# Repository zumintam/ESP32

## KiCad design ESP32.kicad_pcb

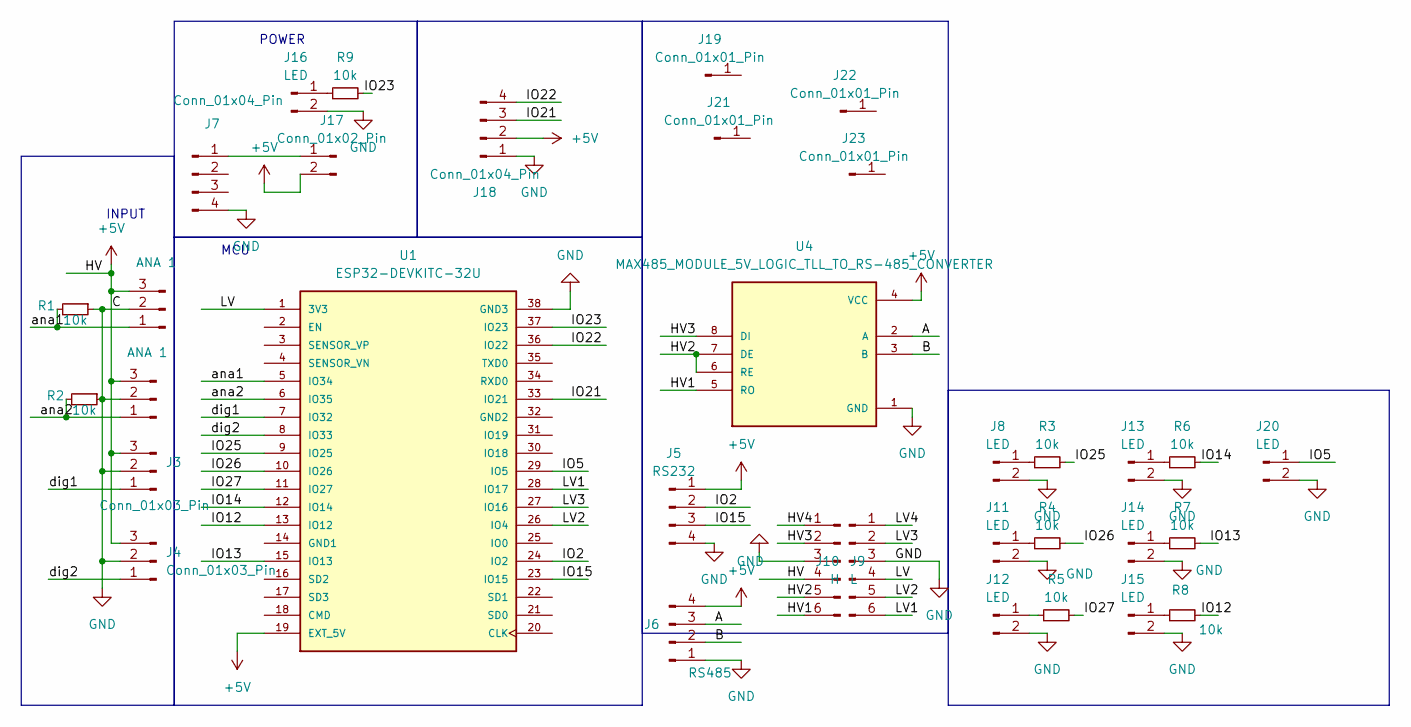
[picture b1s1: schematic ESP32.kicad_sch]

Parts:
J1, J2: ANA 1; JST_EH_S3B-EH_1x03_P2.50mm_Horizontal
J3, J4: Conn_01x03_Pin; JST_EH_S3B-EH_1x03_P2.50mm_Horizontal
J5: RS232; JST_EH_S4B-EH_1x04_P2.50mm_Horizontal
J6: RS485; JST_EH_S4B-EH_1x04_P2.50mm_Horizontal
J7: Conn_01x04_Pin; PinHeader_1x04_P2.54mm_Vertical
J8, J11, J12, J13, J14, J15, J16, J20: LED; JST_XH_B2B-XH-A_1x02_P2.50mm_Vertical
J9: L; PinHeader_1x06_P2.54mm_Vertical
J10: H; PinHeader_1x06_P2.54mm_Vertical
J17: Conn_01x02_Pin; JST_XH_B2B-XH-A_1x02_P2.50mm_Vertical
J18: Conn_01x04_Pin; JST_XH_B4B-XH-A_1x04_P2.50mm_Vertical
J19, J21, J22, J23: Conn_01x01_Pin; MountingHole_2.2mm_M2_Pad
R1, R2, R3, R4, R5, R6, R7, R8, R9: 10k; R_0805_2012Metric
U1: ESP32-DEVKITC-32U; MODULE_ESP32-DEVKITC-32U; PARTREV V4
U4: MAX485_MODULE_5V_LOGIC_TLL_TO_RS-485_CONVERTER; MODULE_MAX485_MODULE_5V_LOGIC_TLL_TO_RS-485_CONVERTER; PARTREV 1r0

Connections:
/A: J6.3, U4.2 (A)
/B: J6.2, U4.3 (B)
/HV1: J9.6, U4.5 (RO)
/HV2: J9.5, U4.6 (RE), U4.7 (DE)
/HV3: J9.2, U4.8 (DI)
/HV4: J9.1
/IO2: J5.2, U1.24 (IO2)
/IO5: J20.1, U1.29 (IO5)
/IO12: R8.2, U1.13 (IO12)
/IO13: R7.2, U1.15 (IO13)
/IO14: R6.2, U1.12 (IO14)
/IO15: J5.3, U1.23 (IO15)
/IO21: J18.3, U1.33 (IO21)
/IO22: J18.4, U1.36 (IO22)
/IO23: R9.2, U1.37 (IO23)
/IO25: R3.2, U1.9 (IO25)
/IO26: R4.2, U1.10 (IO26)
/IO27: R5.2, U1.11 (IO27)
/LV: J10.4, U1.1 (3V3)
/LV1: J10.6, U1.28 (IO17)
/LV2: J10.5, U1.26 (IO4)
/LV3: J10.2, U1.27 (IO16)
/LV4: J10.1
/ana1: J1.1, R1.2, U1.5 (IO34)
/ana2: J2.1, R2.2, U1.6 (IO35)
/dig1: J3.1, U1.7 (IO32)
/dig2: J4.1, U1.8 (IO33)
unnamed: J8.1, R3.1
unnamed: J11.1, R4.1
unnamed: J12.1, R5.1
unnamed: J13.1, R6.1
unnamed: J14.1, R7.1
unnamed: J15.1, R8.1
unnamed: J16.1, R9.1
unnamed: J7.1, J17.1

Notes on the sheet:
POWER
MCU
INPUT

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
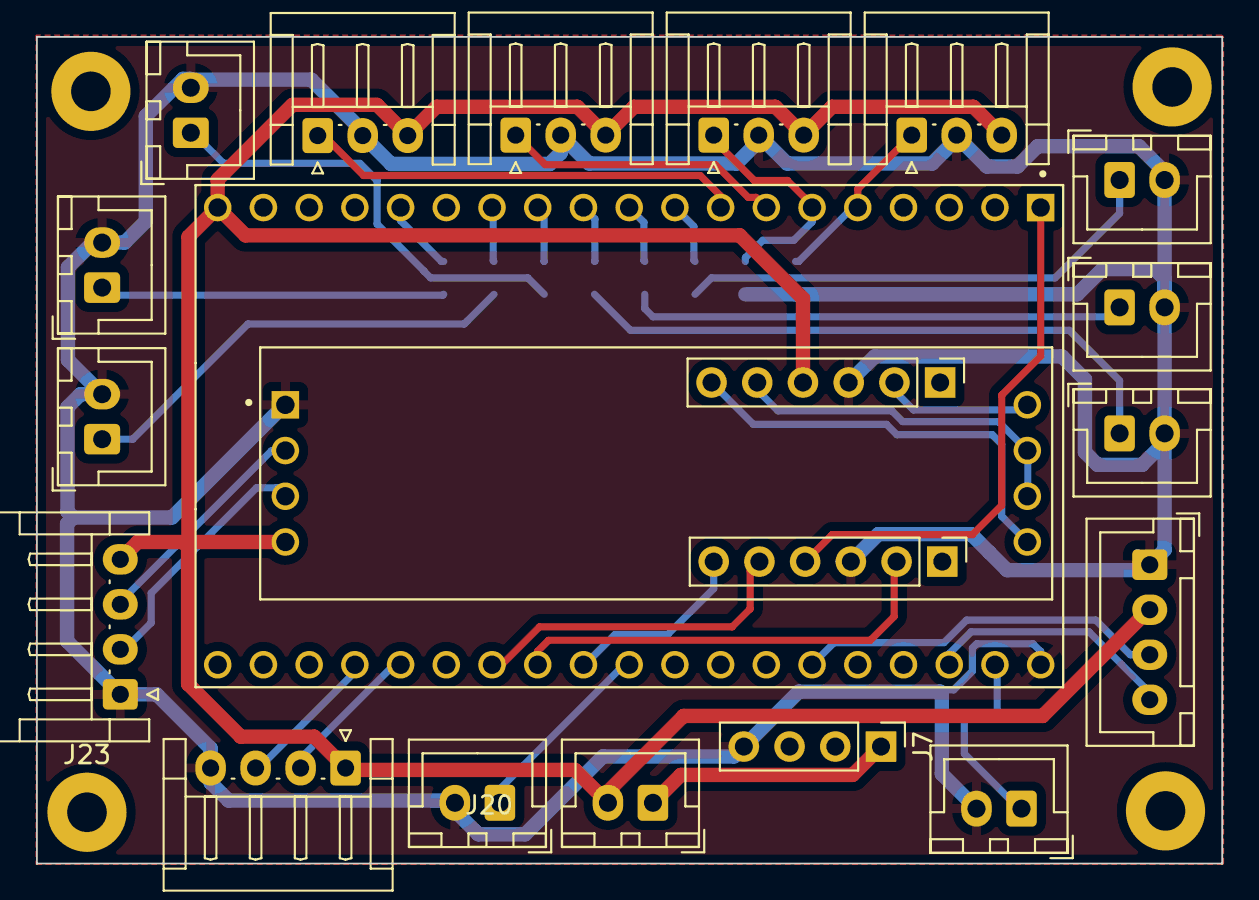
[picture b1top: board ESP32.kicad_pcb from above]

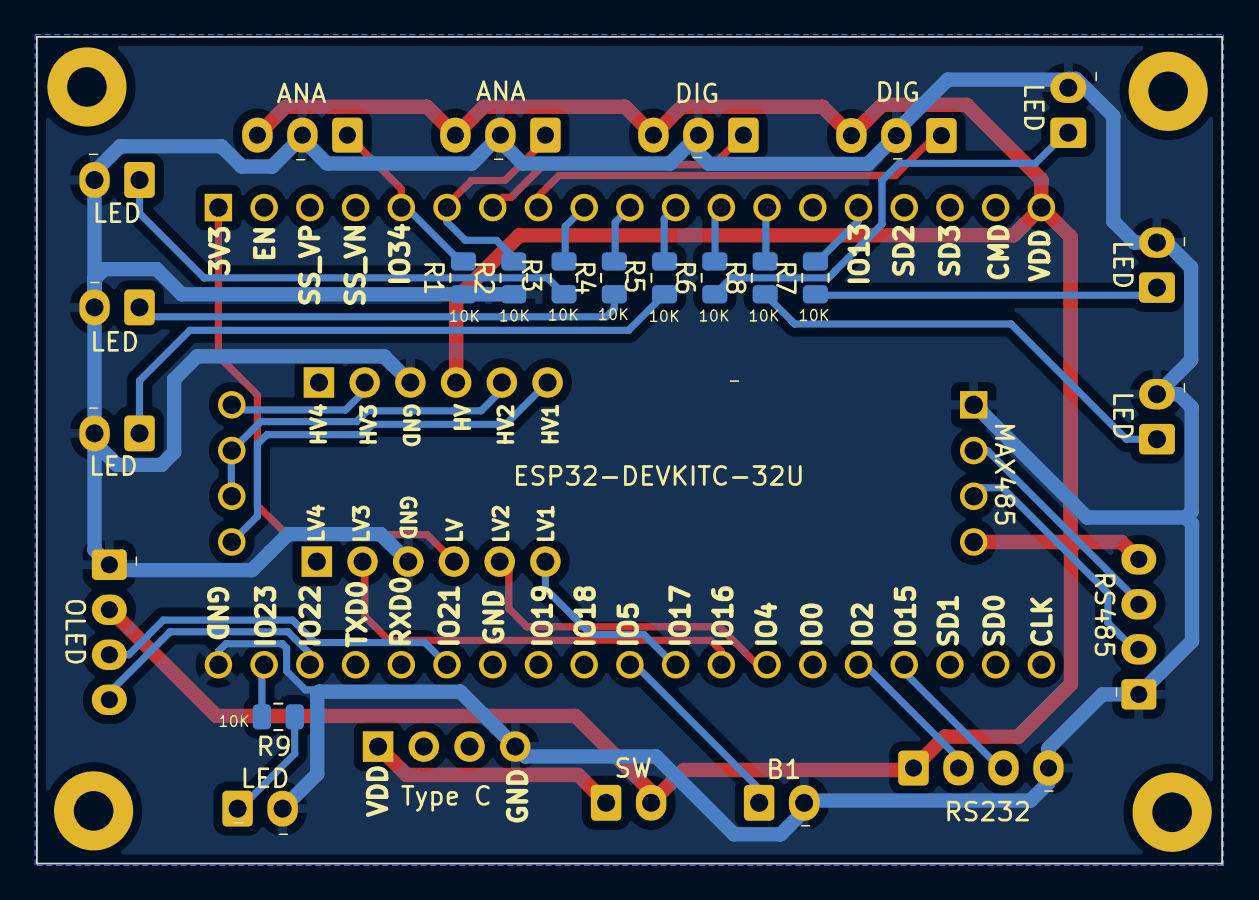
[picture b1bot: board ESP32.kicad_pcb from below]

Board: 2 copper layers, 65.8 x 45.9 mm, 34 parts (9 on the bottom side), 35 nets.
